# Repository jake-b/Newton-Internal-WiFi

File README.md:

# Newton-Internal-WiFi
Design and software for a WiFi board for the Apple Newton MessagePad 2x00

- The PCB design for the board (v1.1)
- The Newton PKG software module for enabling the board in software
- STL files for 3D printing a replacement modem port cover. The original
  port cover interferes with the installed PCB.  I have also included a
  representation of the original port cover, in case you need one.  There
  is a version with supports for printing on a typical hobbiest 
  fused-filament 3D printer.  Trim carefully to size using a razor blade.

# Bill of Materials

- PCB fabricated to 0.8mm thickness
- IW-SMG2SMT-EX - Wireach WiFi / 802.11 Module - External Antenna
- JAE IL-WX-32PB-VF-BE - Internal Connector - No longer available
- LMZ21700SILT - Voltage Regulator Module
- R1 SMD 0603 15k Resistor
- Cout SMD 0805 22uF Capacitor
- Cin, C3 SMD 0805 10uF Capacitor
- Css SMD 0603 3.3nF Capacitor
- C4 SMD 0805 470nF
- Rt SMD 0603 562K ohm 1% Resistor
- Rb SMD 0603 180Kohm 0.5% Resistor
- MC74VHCT50ADT - Buffer
- MC74VHC1G04DFT2G - 1G Inverter
- Resettable Fuses - PPTC 15V 1206 .500A POLYFUSE

# License & Disclaimer
This project is released under the Attribution-NonCommercial-ShareAlike 4.0 
International license.

- Feel free to make your own, or make one for your friends.
- Please release any improvements back to the community.
- Non-commerical use only. Please don't make & sell these at a profit.  If
  by some odd chance you want to make these for sale, please contact me.

As with all of my projects, please use this at your own risk.

BECAUSE THE PROGRAM & HARDWARE DESIGN IS LICENSED FREE OF CHARGE, THERE IS NO 
WARRANTY FOR THE PROGRAM & HARDWARE DESIGN, TO THE EXTENT PERMITTED BY 
APPLICABLE LAW. EXCEPT WHEN OTHERWISE STATED IN WRITING THE COPYRIGHT HOLDERS 
AND/OR OTHER PARTIES PROVIDE THE PROGRAM & HARDWARE DESIGN "AS IS" WITHOUT 
WARRANTY OF ANY KIND, EITHER EXPRESSED OR IMPLIED, INCLUDING, BUT NOT LIMITED 
TO, THE IMPLIED WARRANTIES OF MERCHANTABILITY AND FITNESS FOR A PARTICULAR 
PURPOSE. THE ENTIRE RISK AS TO THE QUALITY AND PERFORMANCE OF THE PROGRAM &
HARDWARE DESIGN IS WITH YOU. SHOULD THE PROGRAM OR HARDWARE DESIGN PROVE 
DEFECTIVE, YOU ASSUME THE COST OF ALL NECESSARY SERVICING, REPAIR OR CORRECTION.

IN NO EVENT UNLESS REQUIRED BY APPLICABLE LAW OR AGREED TO IN WRITING WILL ANY
COPYRIGHT HOLDER, OR ANY OTHER PARTY WHO MAY MODIFY AND/OR REDISTRIBUTE THE 
PROGRAM OR HARDWARE DESIGN AS PERMITTED ABOVE, BE LIABLE TO YOU FOR DAMAGES, 
INCLUDING ANY GENERAL,  SPECIAL, INCIDENTAL OR CONSEQUENTIAL DAMAGES ARISING 
OUT OF THE USE OR INABILITY TO USE THE PROGRAM OR HARDWARE DESIGN (INCLUDING 
BUT NOT LIMITED TO LOSS OF DATA OR DATA BEING RENDERED INACCURATE OR LOSSES 
SUSTAINED BY YOU OR THIRD PARTIES OR A FAILURE OF THE PROGRAM OR HARDWARE 
DESIGN TO OPERATE WITH ANY OTHER PROGRAMS OR HARDWARE), EVEN IF SUCH HOLDER 
OR OTHER PARTY HAS BEEN ADVISED OF THE POSSIBILITY OF SUCH DAMAGES.

The software included toggles low level hardware signals using undocumented 
Newton ROM functions. It is intended for developer use. You should know what 
you're doing, as this could do damage to your hardware.

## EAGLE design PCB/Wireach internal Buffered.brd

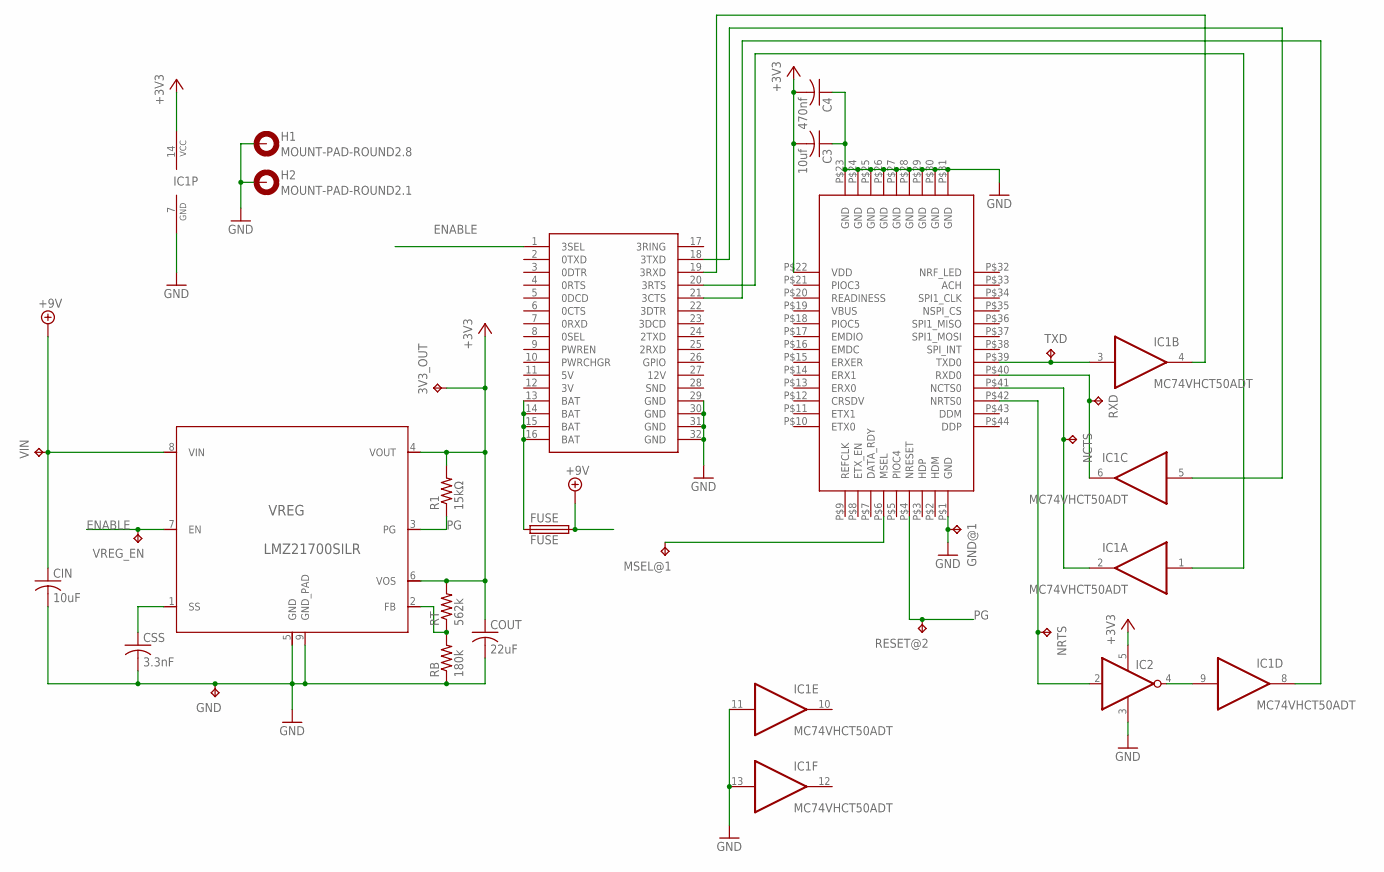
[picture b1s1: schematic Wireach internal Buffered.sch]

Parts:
3V3_OUT: TPTP10R; TP10R
C3: 10uf; C0805
C4: 470nf; C0805
CIN: 10uF; C0805K
COUT: 22uF; C0805K
CSS: 3.3nF; C0603K
FUSE: FUSE; R1206
GND: TPTP10R; TP10R
GND@1: TPTP10R; TP10R
H1: MOUNT-PAD-ROUND2.8; 2,8-PAD
H2: MOUNT-PAD-ROUND2.1; 2,1-PAD
IC1: MC74VHCT50ADT; TSSOP14
IC2: 1G04-DC; SOT353/5
MSEL@1: TPTP10R; TP10R
NCTS: TPTP10R; TP10R
NRTS: TPTP10R; TP10R
R1: 15kΩ; R0603
RB: 180k; R0603
RESET@2: TPTP10R; TP10R
RT: 562k; R0603
RXD: TPTP10R; TP10R
TXD: TPTP10R; TP10R
U$1: WIREACH
U$3: N2-INTOLD; NEWTON
VIN: TPTP10R; TP10R
VREG: LMZ21700SILR; SIL0008B
VREG_EN: TPTP10R; TP10R

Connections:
+3V3: 3V3_OUT.TP, C3.2, C4.2, COUT.1, IC1.14 (VCC), IC2.5 (VDD), R1.2, RT.2, U$1.P$22 (VDD), VREG.4 (VOUT), VREG.6 (VOS)
+9V: CIN.1, FUSE.2, VIN.TP, VREG.8 (VIN)
ENABLE: U$3.1 (3SEL), VREG.7 (EN), VREG_EN.TP
GND: C3.1, C4.1, CIN.2, COUT.2, CSS.2, GND.TP, GND@1.TP, H1.B2,8, H2.B2,8, IC1.7 (GND), IC1.11 (I), IC1.13 (I), IC2.3 (GND), RB.1, U$1.P$1 (GND), U$1.P$23 (GND), U$1.P$24 (GND), U$1.P$25 (GND), U$1.P$26 (GND), U$1.P$27 (GND), U$1.P$28 (GND), U$1.P$29 (GND), U$1.P$30 (GND), U$1.P$31 (GND), U$3.29 (GND), U$3.30 (GND), U$3.31 (GND), U$3.32 (GND), VREG.5 (GND), VREG.9 (GND_PAD)
unnamed: RB.2, RT.1, VREG.2 (FB)
unnamed: CSS.1, VREG.1 (SS)
unnamed: IC1.9 (I), IC2.4 (O)
unnamed: IC1.3 (I), TXD.TP, U$1.P$39 (TXD0)
unnamed: IC2.2 (I), NRTS.TP, U$1.P$42 (NRTS0)
unnamed: FUSE.1, U$3.13 (BAT), U$3.14 (BAT), U$3.15 (BAT), U$3.16 (BAT)
unnamed: IC1.6 (O), RXD.TP, U$1.P$40 (RXD0)
unnamed: IC1.2 (O), NCTS.TP, U$1.P$41 (NCTS0)
unnamed: MSEL@1.TP, U$1.P$6 (MSEL)
NCTS: IC1.1 (I), U$3.20 (3RTS)
NRTS: IC1.8 (O), U$3.21 (3CTS)
PG: R1.1, RESET@2.TP, U$1.P$4 (NRESET), VREG.3 (PG)
RXD: IC1.5 (I), U$3.18 (3TXD)
TXD: IC1.4 (O), U$3.19 (3RXD)

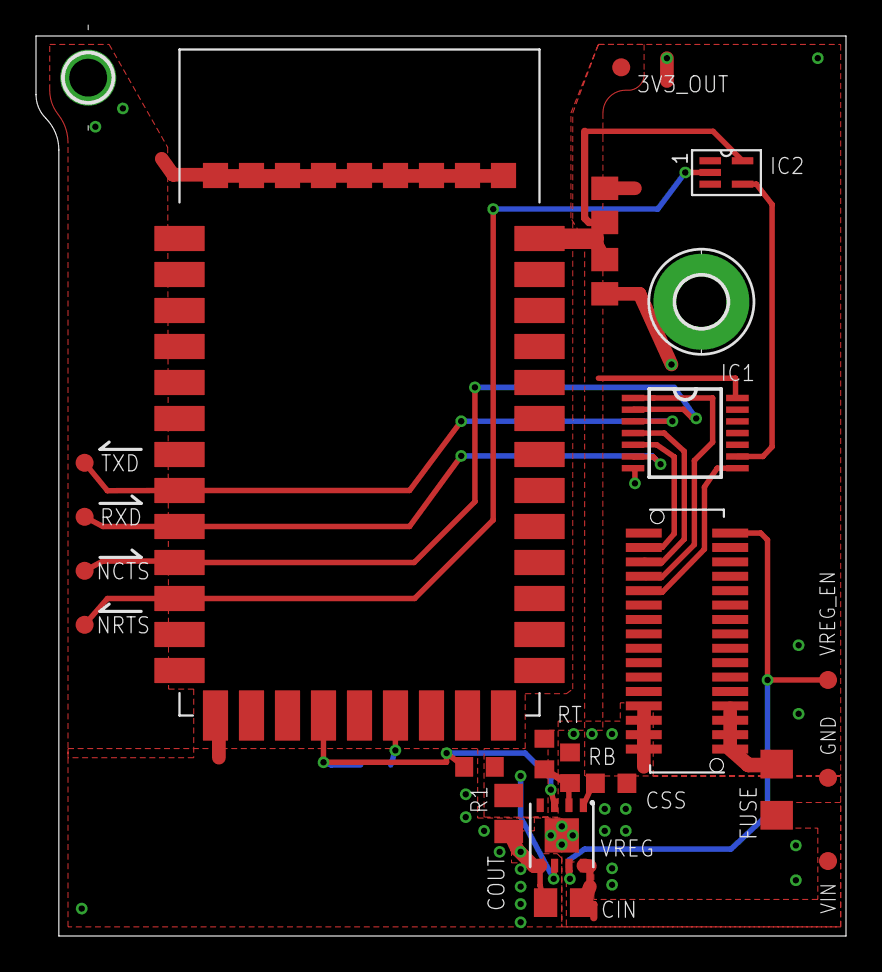
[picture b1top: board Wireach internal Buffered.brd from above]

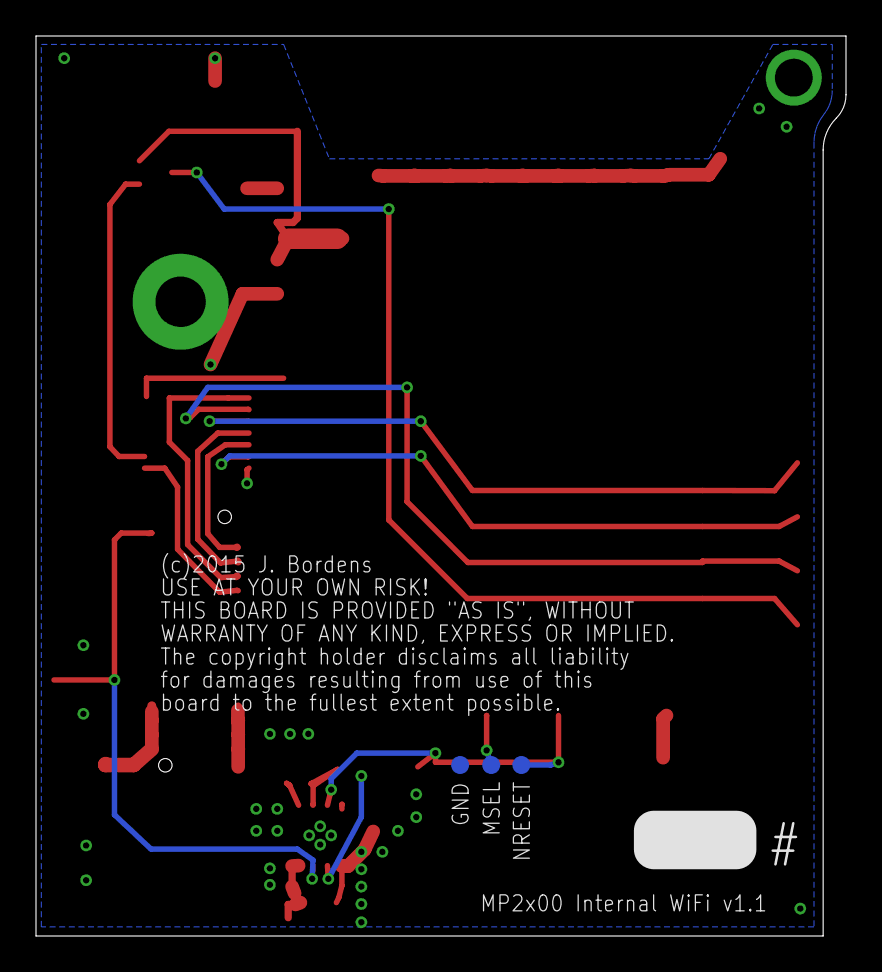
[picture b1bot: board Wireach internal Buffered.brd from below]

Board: 2 copper layers, 45.0 x 50.0 mm, 27 parts (3 on the bottom side), 18 nets.

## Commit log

2015-12-22 The PCB Design, Sofware Package, and 3D models for an interna Newton WiFi board.
2015-12-22 Added Bill of Materials to README
2015-12-22 fixes to BoM
2015-12-23 Added PCB thickness info.

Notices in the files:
PCB/Wireach internal Buffered.brd:
(c)2015 J. Bordens
